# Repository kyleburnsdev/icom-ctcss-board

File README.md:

# Icom IC-229H selectable CTCSS interface

A Pro Micro based interface that adds selectable CTCSS tones to an Icom IC-229H microphone audio path, with PTT forwarding, an encoder, LCD, bypass control and status LEDs.

The schematic and routed PCB prototype are complete; assembly components have been ordered and the PCB is prepared for assembly. The first enclosure iteration is implemented in FreeCAD with print-oriented parts and fit coupons. Pro Micro firmware and a NUCLEO-F767ZI phase-one test driver are implemented, with build, host-test and USB verification. Begin breadboard testing with the [phase-one guide](docs/implementation/firmware-phase1-guide.md); wired timing, UI hardware and analog/radio acceptance remain outstanding. Manufacturing process evidence is recorded separately in the relevant packages.

| Area | Entry point |
| --- | --- |
| Requirements, parts and build instructions | [Project documentation](docs/README.md) |
| Temporary bench assembly and radio-free testing | [Illustrated holder guide](docs/bench-holder-guide.md) and [print package](manufacturing/bench-holder/README.md) |
| Rear-mounted bench display | [B2 replacement panel and printed fasteners](manufacturing/bench-panel-b2/README.md), reusing the B1 base |
| LCD fit correction | [L1 screen-only retest](manufacturing/lcd-fit/README.md), using the measured 9.13 mm projection and corrected hole/window datums |
| Narrow enclosure and radio cradle | [C1 PLA prototype](manufacturing/enclosure-c1/README.md): rotated PCB, corner straps, sliding cover and 12° radio support |
| Electronics | [KiCad project](electronics/icom-ctcss-board.kicad_pro), with project-local libraries beside it |
| Final product harnesses | [Illustrated wiring and termination guide](docs/final-product-wiring-guide.md), with every header connection, wire gauge/color and acceptance checks |
| PCB manufacturing | [Carvera Air package](manufacturing/pcb/carvera-air/README.md) |
| PCB heat transfer | [Fabrication guide](docs/pcb-fabrication-guide.md), [laser transparency](docs/pcb-laser-transparency-guide.md), [sublimation artwork and coupon](manufacturing/pcb/sublimation/README.md) |
| PCB jig / FreeCAD CAM migration | [Required changes and job contract](docs/implementation/pcb-jig-and-freecad-cam.md) |
| Enclosure | [Mechanical workspace](mechanical/enclosure/README.md) |
| Arduino firmware | [Firmware workspace](firmware/README.md) |
| Engineering scripts | [Tools and dependencies](tools/README.md) |
| Repository layout and verification | [Layout notes](docs/implementation/repository-layout.md) |

Open the KiCad project from `electronics/` so its project-local symbol and footprint tables resolve. Keep each manufacturing package together when copying it to another machine.

Original project material is licensed under the [MIT license](LICENSE). Third-party material retains its own terms; see [third-party notices](docs/third-party-notices.md).

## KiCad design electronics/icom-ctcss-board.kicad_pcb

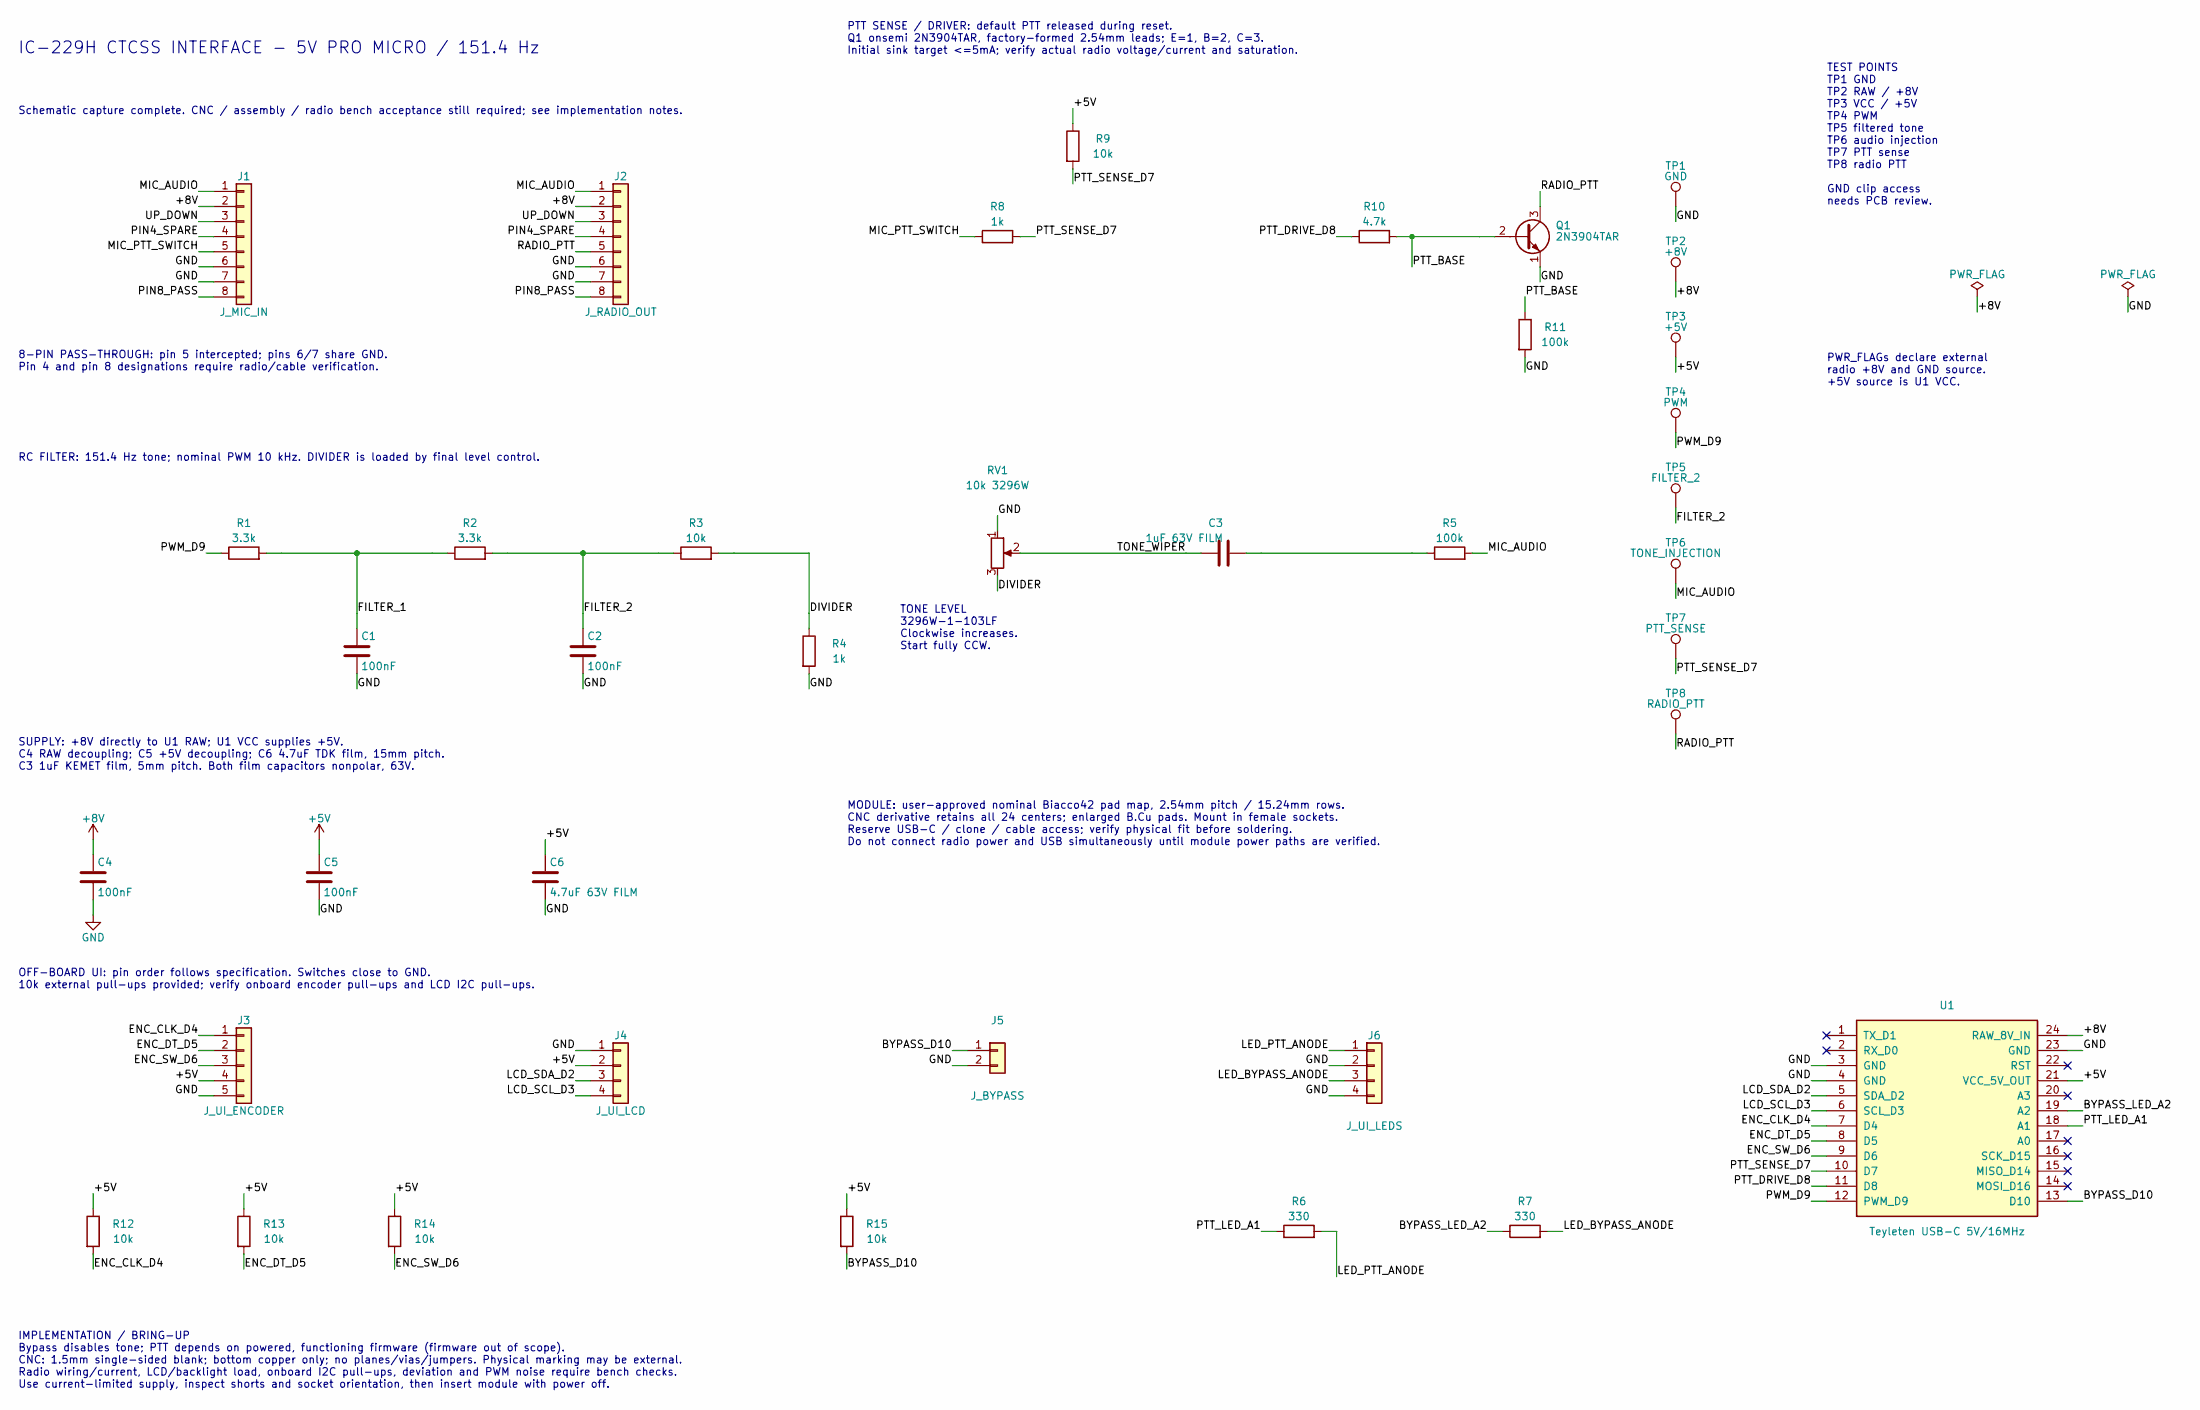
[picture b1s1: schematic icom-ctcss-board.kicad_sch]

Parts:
C1, C2, C4, C5: 100nF; C_Disc_P2.5_CNC; MPN K104K15X7RF5TL2
C3: 1uF 63V FILM; C_Film1u_P5_CNC; MPN R82DC4100AA60J
C6: 4.7uF 63V FILM; C_Film4u7_P15_CNC; MPN B32522C0475J000
J1: J_MIC_IN; Header_1x08_CNC; MPN 61300811121
J2: J_RADIO_OUT; Header_1x08_CNC; MPN 61300811121
J3: J_UI_ENCODER; Header_1x05_CNC; MPN 61300511121
J4: J_UI_LCD; Header_1x04_CNC; MPN 61300411121
J5: J_BYPASS; Header_1x02_CNC; MPN 61300211121
J6: J_UI_LEDS; Header_1x04_CNC; MPN 61300411121
Q1: 2N3904TAR; Q_TO92_Formed_CNC; MPN 2N3904TAR
R1, R2: 3.3k; R_P5.08_CNC; MPN MRS16000C3301FCT00
R3, R9, R12, R13, R14, R15: 10k; R_P5.08_CNC; MPN MRS16000C1002FCT00
R4, R8: 1k; R_P5.08_CNC; MPN MRS16000C1001FCT00
R5, R11: 100k; R_P5.08_CNC; MPN MRS16000C1003FCT00
R6, R7: 330; R_P5.08_CNC; MPN MRS16000C3300FCT00
R10: 4.7k; R_P5.08_CNC; MPN MRS16000C4701FCT00
RV1: 10k 3296W; RV_3296W_CNC; MPN 3296W-1-103LF
TP1: GND; TP_CNC; MPN 61300111121
TP2: +8V; TP_CNC; MPN 61300111121
TP3: +5V; TP_CNC; MPN 61300111121
TP4: PWM; TP_CNC; MPN 61300111121
TP5: FILTER_2; TP_CNC; MPN 61300111121
TP6: TONE_INJECTION; TP_CNC; MPN 61300111121
TP7: PTT_SENSE; TP_CNC; MPN 61300111121
TP8: RADIO_PTT; TP_CNC; MPN 61300111121
U1: Teyleten USB-C 5V/16MHz; ProMicro_CNC_BCu; MPN USB-C Pro Micro 5V 16MHz

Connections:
+5V: C5.1, C6.1, J3.4, J4.2, R9.1, R12.1, R13.1, R14.1, R15.1, TP3.1, U1.21 (VCC_5V_OUT)
+8V: C4.1, J1.2, J2.2, TP2.1, U1.24 (RAW_8V_IN)
/BYPASS_D10: J5.1, R15.2, U1.13 (D10)
/BYPASS_LED_A2: R7.1, U1.19 (A2)
/DIVIDER: R3.2, R4.1, RV1.3
/ENC_CLK_D4: J3.1, R12.2, U1.7 (D4)
/ENC_DT_D5: J3.2, R13.2, U1.8 (D5)
/ENC_SW_D6: J3.3, R14.2, U1.9 (D6)
/FILTER_1: C1.1, R1.2, R2.1
/FILTER_2: C2.1, R2.2, R3.1, TP5.1
/LCD_SCL_D3: J4.4, U1.6 (SCL_D3)
/LCD_SDA_D2: J4.3, U1.5 (SDA_D2)
/LED_BYPASS_ANODE: J6.3, R7.2
/LED_PTT_ANODE: J6.1, R6.2
/MIC_AUDIO: J1.1, J2.1, R5.2, TP6.1
/MIC_PTT_SWITCH: J1.5, R8.1
/PIN4_SPARE: J1.4, J2.4
/PIN8_PASS: J1.8, J2.8
/PTT_BASE: Q1.2 (B), R10.2, R11.1
/PTT_DRIVE_D8: R10.1, U1.11 (D8)
/PTT_LED_A1: R6.1, U1.18 (A1)
/PTT_SENSE_D7: R8.2, R9.2, TP7.1, U1.10 (D7)
/PWM_D9: R1.1, TP4.1, U1.12 (PWM_D9)
/RADIO_PTT: J2.5, Q1.3 (C), TP8.1
/TONE_WIPER: C3.1, RV1.2
/UP_DOWN: J1.3, J2.3
GND: C1.2, C2.2, C4.2, C5.2, C6.2, J1.6, J1.7, J2.6, J2.7, J3.5, J4.1, J5.2, J6.2, J6.4, Q1.1 (E), R4.2, R11.2, RV1.1, TP1.1, U1.3 (GND), U1.4 (GND), U1.23 (GND)
unnamed: C3.2, R5.1

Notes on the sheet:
8-PIN PASS-THROUGH: pin 5 intercepted; pins 6/7 share GND. Pin 4 and pin 8 designations require radio/cable verification.
RC FILTER: 151.4 Hz tone; nominal PWM 10 kHz. DIVIDER is loaded by final level control.
OFF-BOARD UI: pin order follows specification. Switches close to GND. 10k external pull-ups provided; verify onboard encoder pull-ups and LCD I2C pull-ups.
TEST POINTS TP1 GND TP2 RAW / +8V TP3 VCC / +5V TP4 PWM TP5 filtered tone TP6 audio injection TP7 PTT sense TP8 radio PTT GND clip access needs PCB review.
IC-229H CTCSS INTERFACE - 5V PRO MICRO / 151.4 Hz
Schematic capture complete. CNC / assembly / radio bench acceptance still required; see implementation notes.
TONE LEVEL 3296W-1-103LF Clockwise increases. Start fully CCW.
MODULE: user-approved nominal Biacco42 pad map, 2.54mm pitch / 15.24mm rows. CNC derivative retains all 24 centers; enlarged B.Cu pads. Mount in female sockets. Reserve USB-C / clone / cable access; verify physical fit before soldering. Do not connect radio power and USB simultaneously until module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
IMPLEMENTATION / BRING-UP Bypass disables tone; PTT depends on powered, functioning firmware (firmware out of scope). CNC: 1.5mm single-sided blank; bottom copper only; no planes/vias/jumpers. Physical marking may be external. Radio wiring/current, LCD/backlight load, onboard I2C pull-ups, deviatio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
PWR_FLAGs declare external radio +8V and GND source. +5V source is U1 VCC.
PTT SENSE / DRIVER: default PTT released during reset. Q1 onsemi 2N3904TAR, factory-formed 2.54mm leads; E=1, B=2, C=3. Initial sink target <=5mA; verify actual radio voltage/current and saturation.
SUPPLY: +8V directly to U1 RAW; U1 VCC supplies +5V. C4 RAW decoupling; C5 +5V decoupling; C6 4.7uF TDK film, 15mm pitch. C3 1uF KEMET film, 5mm pitch. Both film capacitors nonpolar, 63V.

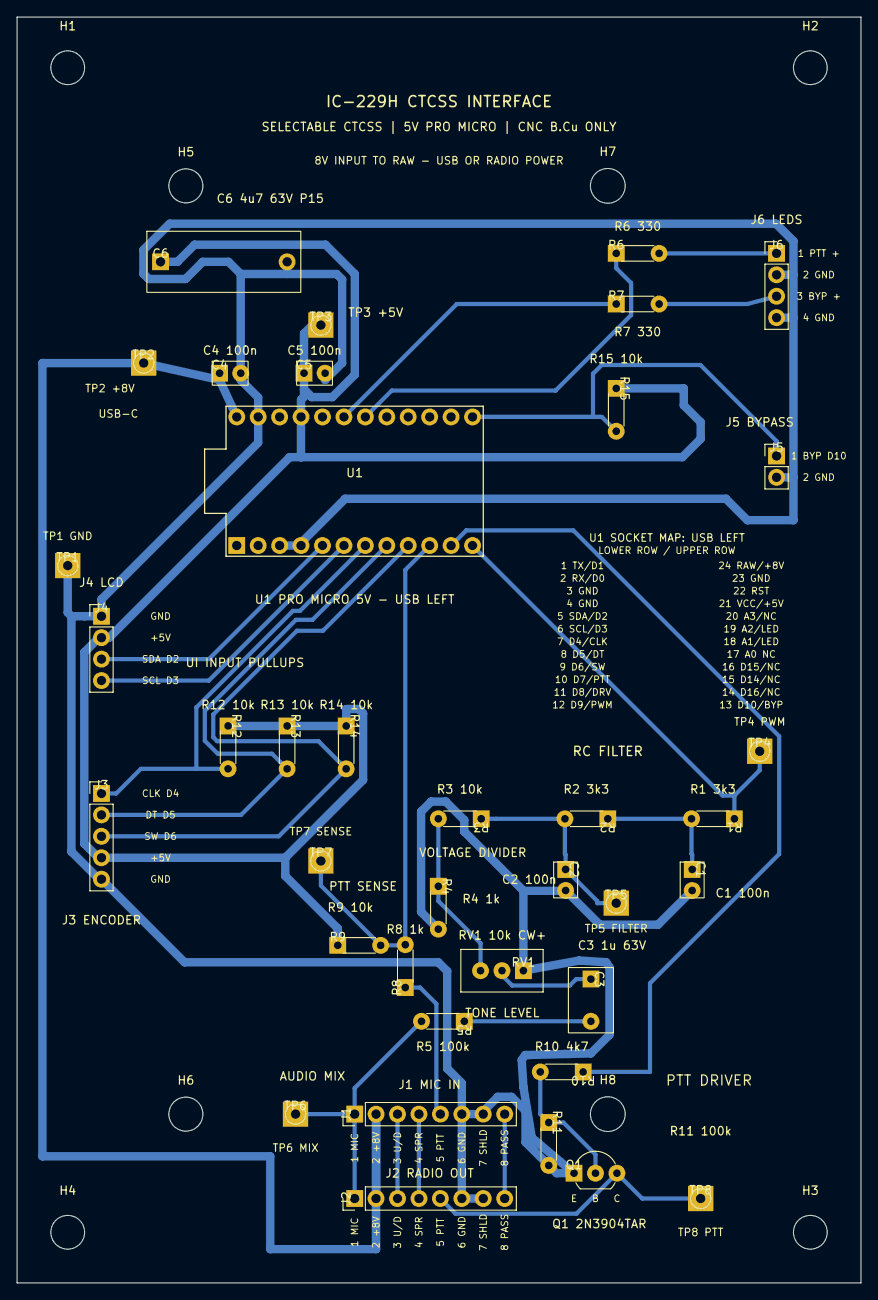
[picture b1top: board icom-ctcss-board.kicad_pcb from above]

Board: 2 copper layers, 100.0 x 150.0 mm, 46 parts (0 on the bottom side), 28 nets.

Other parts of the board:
H1, H2, H3, H4: MountingHole_4mm
H5, H6: JigRegistration_4.03mm
H7, H8: JigRegistration_4.12mm
